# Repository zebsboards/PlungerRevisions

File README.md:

# PincabController Libraries
Libraries written and used for atmega32U4 versions of the plunger
dating back to the V1 through to the V5

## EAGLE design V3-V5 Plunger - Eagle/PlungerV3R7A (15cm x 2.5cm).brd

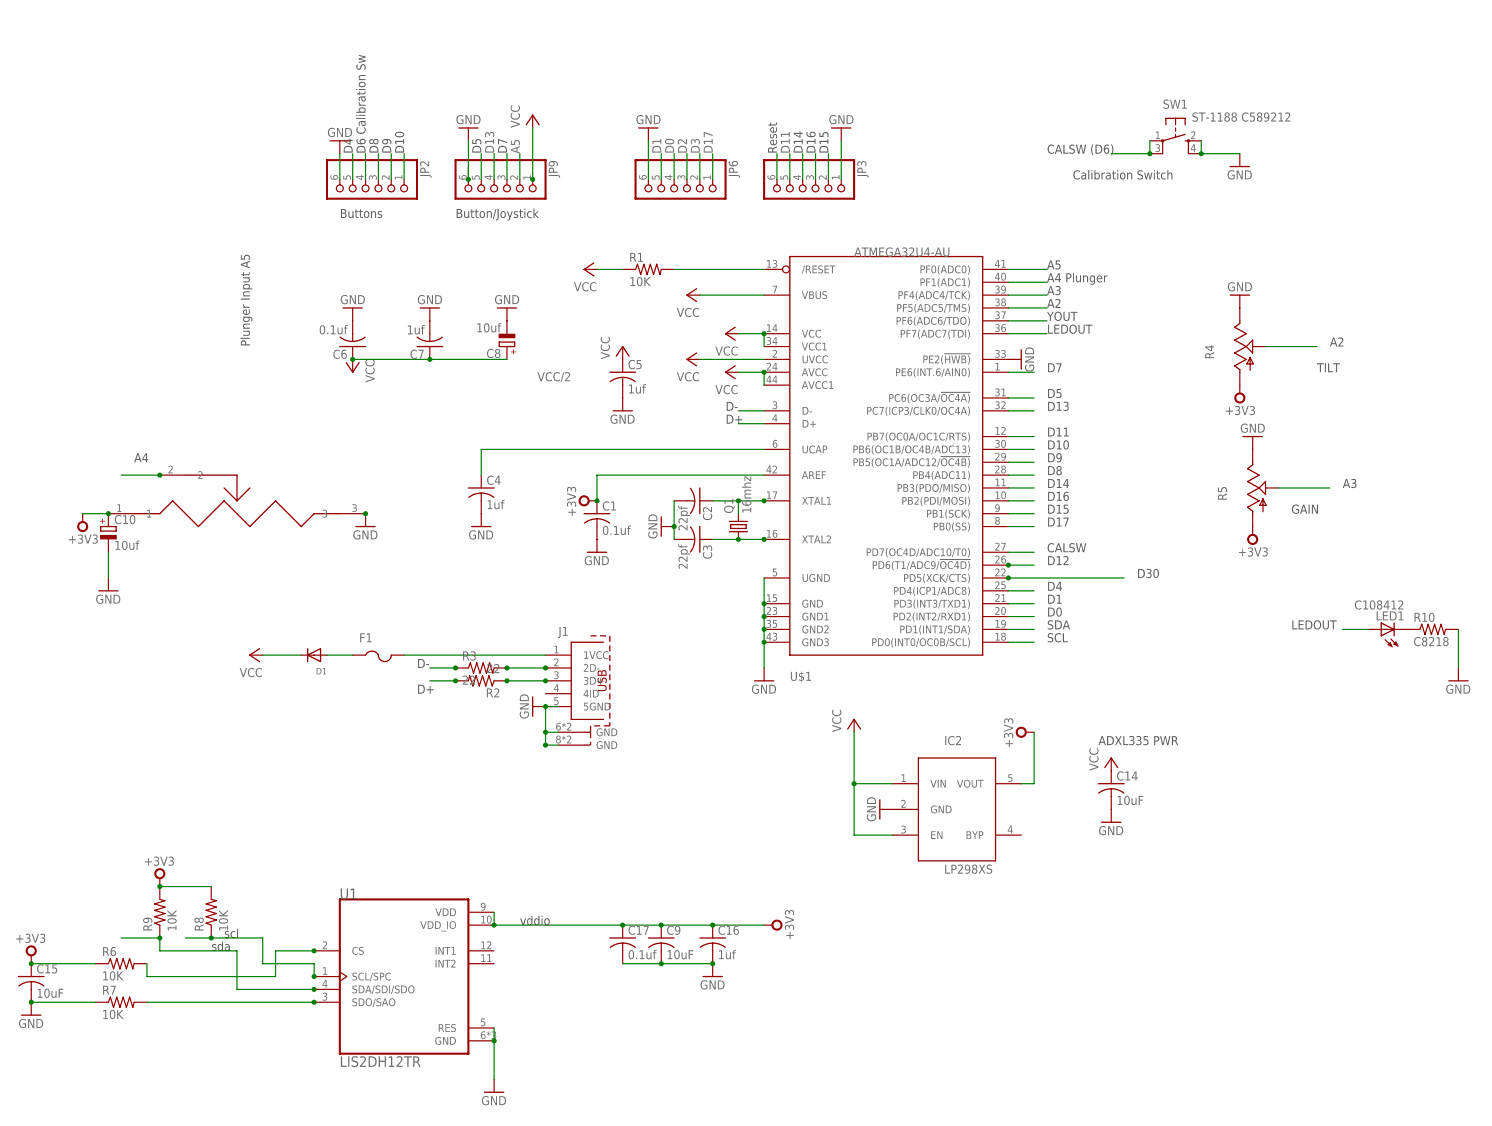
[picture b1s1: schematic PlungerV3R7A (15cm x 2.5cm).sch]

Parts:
C1, C6, C17: 0.1uf; C0603
C2, C3: 22pf; C0603
C4, C5, C7, C16: 1uf; C0603
C8, C10: 10uf; A/3216-18W
C9, C14, C15: 10uF; C0805K
D1: DIODESMA; SMADIODE
F1: PTCFUSE-1812; 1812
IC2: LP298XS; SOT23-5L
J1: 651005136521
JP2, JP3, JP6, JP9: PINHD-1X6B; 1X06-BIG
LED1: C108412; CHIP-LED0805
Q1: 16mhz; CTS406
R1: 10K; M0805
R2, R3: 22; R0603
R4, R5: TRIM_US-B25P; B25P
R6: 10K; R0805
R7, R8, R9: 10K; R0603
R10: C8218; M0805
SW1: ST-1188 C589212; KMR2
U1: LIS2DH12TR; PQFN50P200X200100-12N
U$1: ATMEGA32U4-AU; TQFP44
U$7: PS100POTENTIOMETER; PS100

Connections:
+3V3: C1.1, C9.1, C10.+, C15.1, C16.1, C17.1, IC2.5 (VOUT), R4.A, R5.A, R6.1, R8.2, R9.2, U1.9 (VDD), U1.10 (VDD_IO), U$1.42 (AREF), U$7.1
A2: R4.S, U$1.38 (PF5(ADC5/TMS))
A3: R5.S, U$1.39 (PF4(ADC4/TCK))
A4: U$1.40 (PF1(ADC1)), U$7.2
A5: JP9.2, U$1.41 (PF0(ADC0))
CALSW: JP2.4, SW1.1, SW1.3 (P1), U$1.27 (PD7(OC4D/ADC10/T0))
D0: JP6.4, U$1.20 (PD2(INT2/RXD1))
D1: JP6.5, U$1.21 (PD3(INT3/TXD1))
D4: JP2.5, U$1.25 (PD4(ICP1/ADC8))
D5: JP9.5, U$1.31 (PC6(OC3A/!OC4A))
D7: JP9.3, U$1.1 (PE6(INT.6/AIN0))
D8: JP2.3, U$1.28 (PB4(ADC11))
D9: JP2.2, U$1.29 (PB5(OC1A/ADC12/!OC4B))
D10: JP2.1, U$1.30 (PB6(OC1B/OC4B/ADC13))
D11: JP3.5, U$1.12 (PB7(OC0A/OC1C/RTS))
D12: U$1.26 (PD6(T1/ADC9/!OC4D))
D13: JP9.4, U$1.32 (PC7(ICP3/CLK0/OC4A))
D14: JP3.4, U$1.11 (PB3(PDO/MISO))
D15: JP3.2, U$1.9 (PB1(SCK))
D16: JP3.3, U$1.10 (PB2(PDI/MOSI))
D17: JP6.1, U$1.8 (PB0(SS))
D30: U$1.22 (PD5(XCK/CTS))
D+: R2.2, U$1.4 (D+)
D-: R3.1, U$1.3 (D-)
GND: C1.2, C2.2, C3.2, C4.2, C5.2, C6.2, C7.2, C8.-, C9.2, C10.-, C14.2, C15.2, C16.2, C17.2, IC2.2 (GND), J1.5 (5GND), J1.6 (GND), J1.7 (GND), J1.8 (GND), J1.9 (GND), JP2.6, JP3.1, JP6.6, JP9.6, R4.E, R5.E, R7.1, R10.2, SW1.2 (S), SW1.4 (S1), U1.5 (RES), U1.6 (GND), U1.7 (GND), U1.8 (GND), U$1.5 (UGND), U$1.15 (GND), U$1.23 (GND1), U$1.33 (PE2(!HWB)), U$1.35 (GND2), U$1.43 (GND3), U$7.3
LEDOUT: LED1.A, U$1.36 (PF7(ADC7(TDI))
unnamed: R7.2, U1.3 (SDO/SAO)
unnamed: C2.1, Q1.3 (2), U$1.17 (XTAL1)
unnamed: C3.1, Q1.1, U$1.16 (XTAL2)
unnamed: J1.3 (3D+), R2.1
unnamed: C4.1, U$1.6 (UCAP)
unnamed: J1.2 (2D-), R3.2
unnamed: F1.2, J1.1 (1VCC)
unnamed: D1.A, F1.1
unnamed: R6.2, U1.2 (CS)
unnamed: LED1.C, R10.1
RST: JP3.6, R1.2, U$1.13 (/RESET)
SCL: JP6.2, R8.1, U1.1 (SCL/SPC), U$1.18 (PD0(INT0/OC0B/SCL))
SDA: JP6.3, R9.1, U1.4 (SDA/SDI/SDO), U$1.19 (PD1(INT1/SDA))
VCC: C5.1, C6.1, C7.1, C8.+, C14.1, D1.C, IC2.1 (VIN), IC2.3 (EN), JP9.1, R1.1, U$1.2 (UVCC), U$1.7 (VBUS), U$1.14 (VCC), U$1.24 (AVCC), U$1.34 (VCC1), U$1.44 (AVCC1)
YOUT: U$1.37 (PF6(ADC6/TDO))

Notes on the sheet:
Plunger Input A5
YOUT
LEDOUT
CALSW
D10
D11
D12
D13
D14
D15
D16
D17
Button/Joystick
D6 Calibration Sw
Buttons
A4 Plunger
VCC/2
D30
Reset
GAIN
TILT
ADXL335 PWR
SDA
SCL
CALSW (D6)
Calibration Switch
sda
scl
vddio

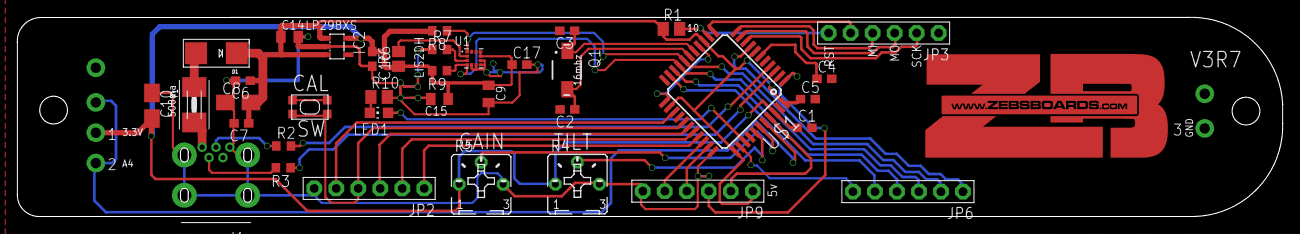
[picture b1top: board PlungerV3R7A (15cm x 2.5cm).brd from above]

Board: 2 copper layers, 145.9 x 22.9 mm, 39 parts (0 on the bottom side), 38 nets.

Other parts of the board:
U$2: ZB_HUGE_COPPER

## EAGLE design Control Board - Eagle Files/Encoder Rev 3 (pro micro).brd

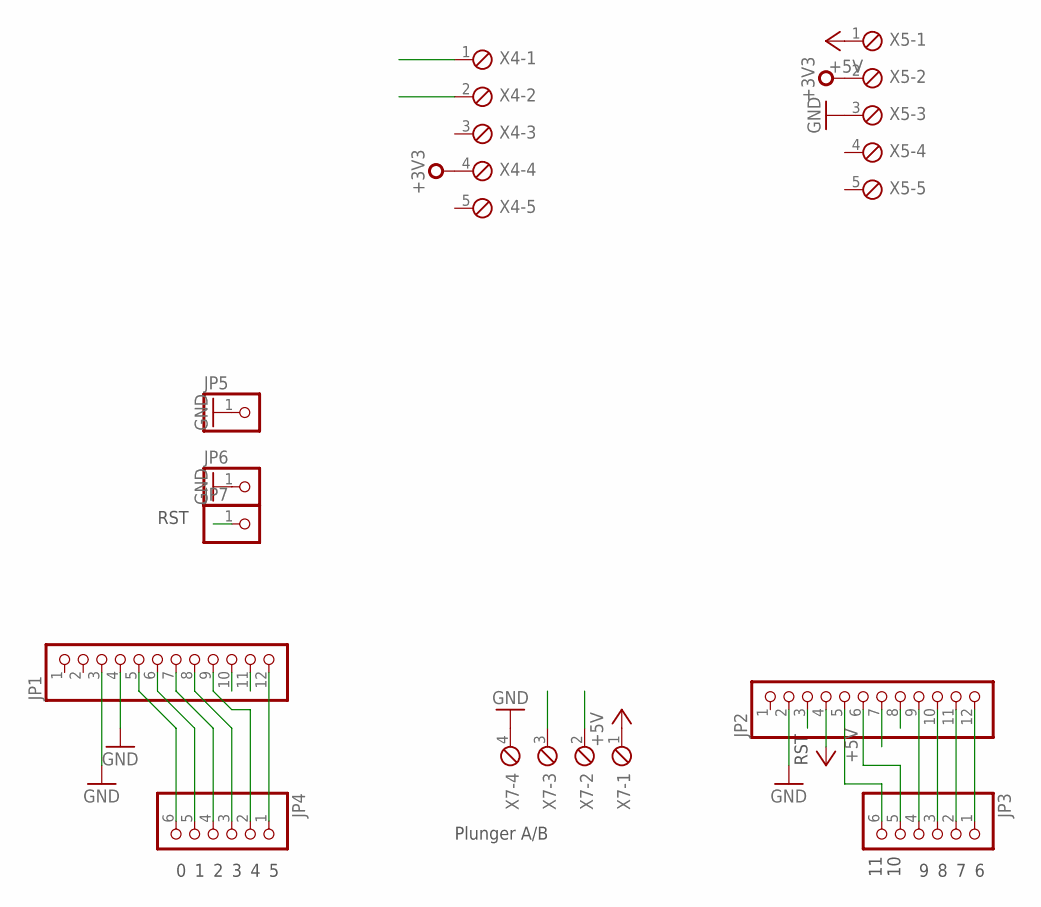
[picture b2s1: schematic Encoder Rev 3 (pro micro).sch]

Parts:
JP1, JP2: PINHD-1X12-CB; 1X12-CB
JP3, JP4: PINHD-1X6B; 1X06-BIG
JP5, JP6, JP7: PINHD-1X1CB; 1X01-CLEANBIG
X4, X5: MPT5; 5POL254
X7: MPT4; 4POL254

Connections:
+3V3: X4.4, X5.2
+5V: JP2.4, X5.1, X7.1
A: JP1.10, X7.3
B: JP1.11, X7.2
GND: JP1.3, JP1.4, JP2.2, JP5.1, JP6.1, X5.3, X7.4
unnamed: JP1.12, JP4.1
unnamed: JP1.9, JP4.2
unnamed: JP1.8, JP4.3
unnamed: JP1.7, JP4.4
unnamed: JP1.6, JP4.5
unnamed: JP1.5, JP4.6
unnamed: JP2.12, JP3.1
unnamed: JP2.11, JP3.2
unnamed: JP2.10, JP3.3
unnamed: JP2.9, JP3.4
unnamed: JP2.6, JP3.5
unnamed: JP2.5, JP3.6
RST: JP2.3, JP7.1
XOUT: JP2.8, X4.1
YOUT: JP2.7, X4.2

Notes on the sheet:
Plunger A/B
RST

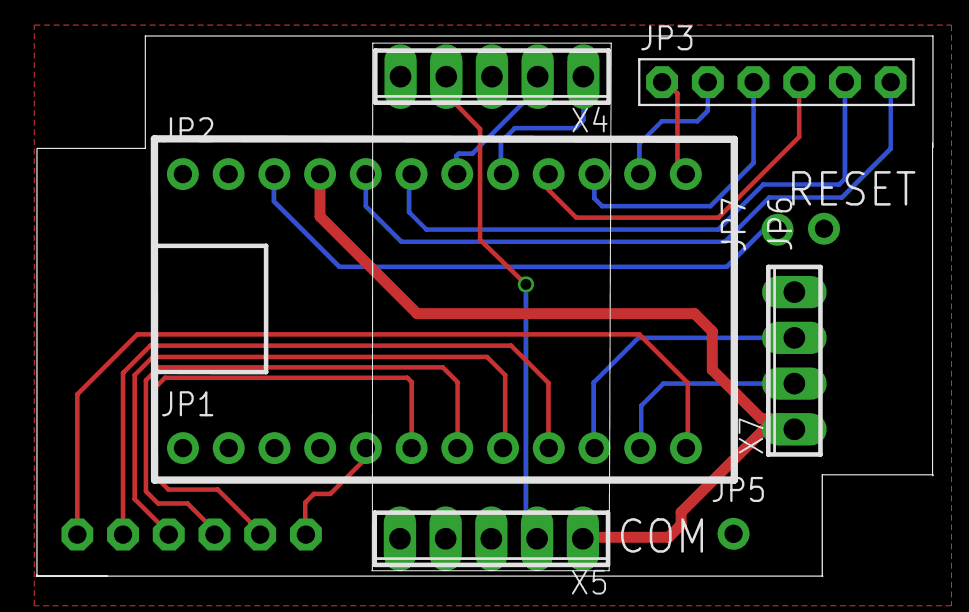
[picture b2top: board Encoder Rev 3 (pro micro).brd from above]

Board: 2 copper layers, 49.8 x 30.0 mm, 10 parts (1 on the bottom side), 20 nets.

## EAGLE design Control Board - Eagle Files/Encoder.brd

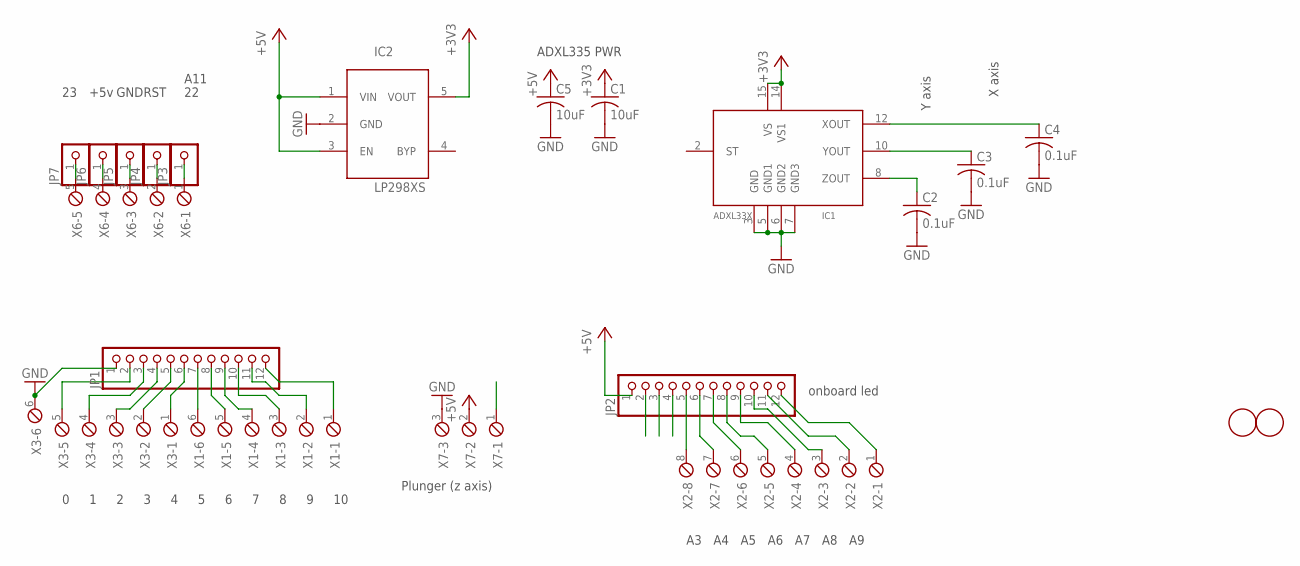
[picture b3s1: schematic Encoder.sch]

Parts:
C1, C5: 10uF; C0805K
C2, C3, C4: 0.1uF; C0805K
IC1: ADXL33X; 16LCSP
IC2: LP298XS; SOT23-5L
JP1, JP2: PINHD-1X12-CB; 1X12-CB
JP3, JP4, JP5, JP6, JP7: PINHD-1X1CB; 1X01-CLEANBIG
U$1, U$2: FIDUCIAL; FIDUCIAL_1MM
X1, X3: MPT6; 6POL254
X2: MPT8; 8POL254
X6: MPT5; 5POL254
X7: MPT3; 3POL254

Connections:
+3V3: C1.1, IC1.14 (VS1), IC1.15 (VS), IC2.5 (VOUT)
+5V: C5.1, IC2.1 (VIN), IC2.3 (EN), JP2.1, X7.2
GND: C1.2, C2.2, C3.2, C4.2, C5.2, IC1.3 (GND), IC1.5 (GND1), IC1.6 (GND2), IC1.7 (GND3), IC2.2 (GND), JP1.1, X3.6, X7.3
unnamed: JP2.5, X2.8
unnamed: JP2.6, X2.7
unnamed: JP2.7, X2.6
unnamed: JP2.8, X2.5
unnamed: JP2.9, X2.4
unnamed: JP2.10, X2.3
unnamed: JP2.11, X2.2
unnamed: JP7.1, X6.5
unnamed: JP6.1, X6.4
unnamed: JP5.1, X6.3
unnamed: JP4.1, X6.2
unnamed: JP3.1, X6.1
unnamed: JP1.2, X3.5
unnamed: JP1.3, X3.4
unnamed: JP1.4, X3.3
unnamed: JP1.5, X3.2
unnamed: JP1.6, X3.1
unnamed: JP1.7, X1.6
unnamed: JP1.8, X1.5
unnamed: JP1.9, X1.4
unnamed: JP1.10, X1.3
unnamed: JP1.11, X1.2
unnamed: JP1.12, X1.1
unnamed: JP2.12, X2.1
XOUT: C4.1, IC1.12 (XOUT), JP2.2
YOUT: C3.1, IC1.10 (YOUT), JP2.3
ZIN: JP2.4, X7.1
ZOUT: C2.1, IC1.8 (ZOUT)

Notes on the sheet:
Plunger (z axis)
X axis
Y axis
onboard led
ADXL335 PWR
+5v
GND
RST
A11

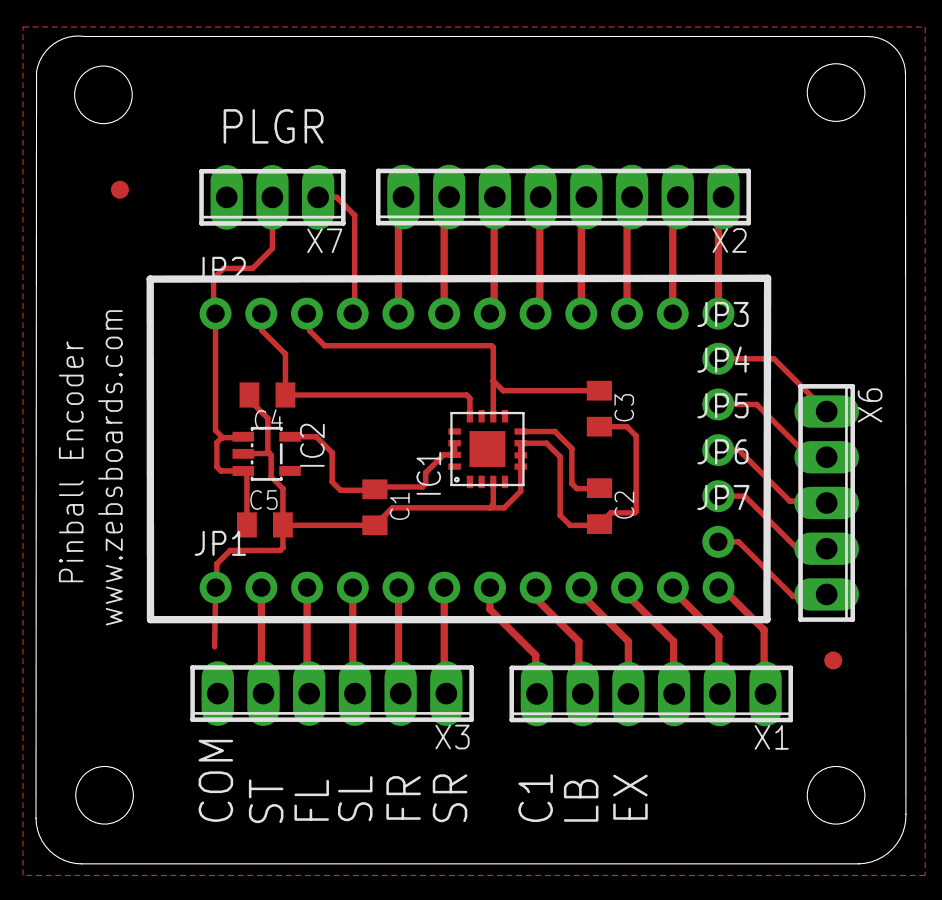
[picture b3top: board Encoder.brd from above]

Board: 2 copper layers, 48.3 x 46.0 mm, 21 parts (0 on the bottom side), 31 nets.

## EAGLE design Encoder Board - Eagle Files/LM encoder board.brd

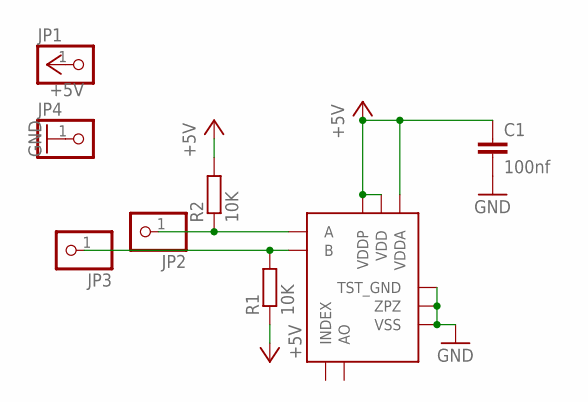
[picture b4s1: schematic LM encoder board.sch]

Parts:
C1: 100nf; C0805
JP1, JP2, JP3, JP4: PINHD-1X1CB; 1X01-CLEANBIG
R1, R2: 10K; M0805
U1: AS5304_AS5306SSOP20; AS5304_5306

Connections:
+5V: C1.1, JP1.1, R1.1, R2.2, U1.3 (VDDP), U1.7 (VDD), U1.16 (VDDA)
GND: C1.2, JP4.1, U1.1 (VSS), U1.15 (TST_GND), U1.20 (ZPZ)
unnamed: JP2.1, R2.1, U1.2 (A)
unnamed: JP3.1, R1.2, U1.4 (B)

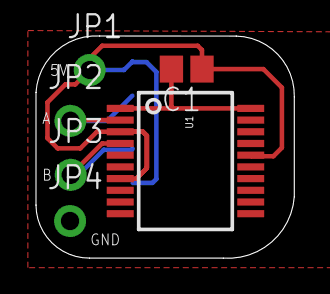
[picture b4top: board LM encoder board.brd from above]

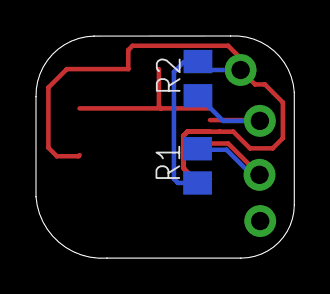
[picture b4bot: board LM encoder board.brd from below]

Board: 2 copper layers, 14.3 x 12.3 mm, 8 parts (2 on the bottom side), 4 nets.

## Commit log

2024-11-28 Initial README.md
2025-07-08 Add files via upload
    STL files for 3D printed parts
2025-07-08 Add files via upload
    3D printable V4 STLs
2025-07-08 V2 3D printable STLs
2025-07-08 3D STLs for intehgrated ball shooter version
2025-07-10 VirtuaPin v4plunger Configuration Utility Source
2025-07-13 Pincab Usb descriptor files

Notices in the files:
parts and their libraries:
Wurth_Elektronik_Electromechanic_Input-O: Copyright: Würth Elektronik
